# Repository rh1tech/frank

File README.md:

# FRANK

FRANK is a hardware emulation platform built around the Raspberry Pi RP2350 (Pico 2 modules and RP2350A QFN). RP2040 / Pico still works in FRANK's socket, but in practice only a handful of firmware (mainly the older ZX Spectrum cores) still targets RP2040. Everything modern (IBM PC, NES, SNES, Genesis, the DOOM / id Tech 1 ports, FRANK OS, and so on) is RP2350-only.

It started as a fork of the [Murmulator](https://murmulator.tilda.ws/) project by [Alex Ekb](https://t.me/Alex_Eburg). Over time it picked up extra video outputs, audio paths, USB and WiFi support, and several form factors.

The name comes from "Frankenstein". The board is stitched together from parts of different projects, so the name stuck.

## Looking for an older board?

This repository now ships only the boards under `hardware/` that are actively maintained. The `accessories/` and `archive/` directories are gone. Older revisions, retired boards, and accessory adapters such as HDMI2VGA and USB2PS2 live in [rh1tech/frank-archive](https://github.com/rh1tech/frank-archive).

Experimental and work-in-progress designs live in [rh1tech/frank-lab](https://github.com/rh1tech/frank-lab).

## The boards in this repo

Ten maintained boards and one published prototype, each with its own KiCad project, gerbers, BOM and assembly drawings, plus two add-on modules ([TurboSound](#modules) and [Hecate](#modules)) and three [retro-CPU boards](#retro-cpu-boards).

| Board | Render | PCB size | Compute | Best for |
|-------|:------:|----------|---------|----------|
| [FRANK Next](./hardware/frank_next) |  | 99.0 × 53.98 mm | RP2350B + RP2350A, both on-board | **Flagship.** Two RP2350 dies, on-board ESP8266EX WiFi, CH343P console, three USB-A host ports. |
| [MegaFRANK](./hardware/megafrank) |  | 149.9 × 99.5 mm | Pimoroni PGA2350 (RP2350B module) | Maximal board — every output plus on-board dual-AY TurboSound, DS3231 RTC and dual power input. |
| [FRANK PGA](./hardware/frank_pga) |  | 99.5 × 83.1 mm | Pimoroni PGA2350 (RP2350A module) | Every output on one PCB, native USB host with multiplexer, ESD-protected. |
| [FRANK](./hardware/frank) |  | 99.5 × 83.1 mm | Raspberry Pi Pico / Pico 2 (socket) + RP2040-Zero | Socketed alternative. Easiest to solder, swap Pico modules at will, USB-to-PS/2 helper on board. |
| [Old Skool FRANK](./hardware/oldskool) |  | 100.0 × 79.0 mm | Pimoroni PGA2350 (RP2350B module) | The retro-connector board: HDMI **and** VGA, hardware PS/2, DB9 gamepad. Only 2-layer design, easiest to hand-assemble. |
| [MiniFRANK](./hardware/minifrank) |  | 85.6 × 53.98 mm | RP2350A QFN, on-board | Compact full-feature board with WiFi, VGA, HDMI and one gamepad port. |
| [FRANK Core 2U](./hardware/frank_core2u) |  | 67.0 × 55.0 mm | RP2350B + RP2350A, both on-board | Smallest usable dual-die board. Video, sound, storage and USB only — no WiFi, no RTC. |
| [FRANK Core 2 Proto](./hardware/frank_core2_proto) |  | 55.0 × 55.0 mm | RP2350B + RP2350A, both on-board | Prototype. Core 2U without the USB host side — the dual-die topology at its smallest. |
| [MicroFRANK](./hardware/microfrank) |  | 32 × 74 mm | RP2350A QFN, on-board | Smallest single-die board. HDMI only, no hardware PS/2 or DB9 gamepad. Keyboards, mice and gamepads connect over the stacked USB host. |
| [ZeroFRANK](./hardware/zerofrank) |  | 65 × 25 mm | RP2350A QFN, on-board | Smallest RP2350A board. HDMI only, USB host for input, on-board flash + PSRAM + I²S audio. |
| [Nyx](./hardware/nyx) |  | 51 × 21 mm | RP2350B QFN, on-board | Open-source Pico 2 clone with built-in PSRAM. Drop-in replacement for Pico Plus 2 in the FRANK socket. |

The full-size and compact boards use the M2 GPIO layout, so any firmware build for M2 runs on them (subject to the feature differences below). FRANK Next, Core 2U and Core 2 Proto are the exception: they carry two RP2350 dies and firmware must be built for that split, or the slave simply sits idle. Nyx is a compute module — it plugs into the FRANK socket and provides the RP2350B, flash and PSRAM; the FRANK motherboard provides all the I/O.

### Comparison: full-size boards

| Feature | MegaFRANK | FRANK PGA | FRANK | Old Skool |
|---------|:---------:|:---------:|:-----:|:---------:|
| Compute | Pimoroni PGA2350 | Pimoroni PGA2350 | Pico / Pico 2 (socket) | Pimoroni PGA2350 |
| Copper layers | 4 | 4 | 4 | **2** |
| On-board flash | via module | via module | via module | via module |
| On-board PSRAM | via module | via module | via module | via module |
| HDMI output | Yes | Yes | Yes | Yes |
| VGA output | Yes | Yes | Yes | Yes |
| Composite (RCA) | Yes | Yes | Yes | — |
| TFT display header | Yes | Yes | Yes | — |
| Hardware PS/2 port | Yes | Yes | Yes | Yes |
| USB-emulated PS/2 (RP2040-Zero) | — | — | Yes | — |
| Gamepad ports (DB9) | 2 | 2 | 2 | 1 |
| Stacked USB Type-A host | Yes | Yes | Yes | Yes |
| USB hub | MW7211A | MW7211A | MW7211A | MW7211A |
| USB host multiplexer | 74HC4052D | 74HC4052D | — | 74HC4052 |
| USBLC6 ESD protection | Yes | Yes | — | — |
| WiFi | ESP-01S socket | ESP-01S socket | ESP-01S socket | ESP-01S socket |
| Real-time clock | DS3231 | — | — | — |
| Tape input (3.5mm) | Yes | Yes | Yes | Yes |
| Audio DAC | TDA1387 | TDA1387 | TDA1387 | TDA1545A + LM358 |
| PAM8403 speaker amp | Yes | Yes | Yes | — |
| Power input | DC barrel jack (×2) | DC barrel jack | DC barrel jack | USB-C / USB-B |
| Voltage regulator | MP1584 buck + AMS1117 LDO | MP1584 buck + AMS1117 LDO | MP1584 buck + AMS1117 LDO | AMS1117 LDO |
| Mounting holes | 4 × 2.7 mm | 4 × 2.7 mm | 4 × 2.7 mm | 4 × 2.7 mm |

On-board TurboSound (dual YM2149), a DS3231 real-time clock and a DS2401 silicon serial number are unique to MegaFRANK. Old Skool FRANK is the only 2-layer board in the repo, which makes it the friendliest to hand-assembly and rework.

### Comparison: compact boards

| Feature | FRANK Next | MiniFRANK | Core 2U | Core 2 Proto | MicroFRANK | ZeroFRANK |
|---------|:----------:|:---------:|:-------:|:------------:|:----------:|:---------:|
| Compute | RP2350B + RP2350A | RP2350A QFN | RP2350B + RP2350A | RP2350B + RP2350A | RP2350A QFN | RP2350A QFN |
| On-board flash | 2 × W25Q128 | W25Q128 | 2 × W25Q128 | 2 × W25Q128 | W25Q128 | W25Q128 |
| On-board PSRAM | 2 × 8 MB | 8 MB | 2 × 8 MB | 2 × 8 MB | 8 MB | 8 MB |
| HDMI output | Yes | Yes | Yes | Yes | Yes | Yes |
| VGA output | — | Yes | — | — | — | — |
| Hardware PS/2 port | — | Yes | — | — | — | — |
| Gamepad ports (DB9) | — | 1 | — | — | — | — |
| USB Type-A host ports | 3 | 2 (stacked) | 2 | — | 2 (stacked) | — (USB-C PIO host) |
| USB hub | CH334F | MW7211A | MW7211A | — | MW7211A | — |
| USB host multiplexer | TS3USB221 × 2 | TS3USB221 | TS3USB221 | — | TS3USB221 | — |
| USB serial bridge | CH343P | — | — | — | — | — |
| WiFi | ESP8266EX on-board | ESP-01S socket | — | — | — | — |
| Real-time clock | DS3231MZ | — | — | — | — | — |
| Tape input (3.5mm) | Yes | Yes | Yes | — | — | — |
| Audio DAC | TLV320DAC3100 | TDA1387 | TDA1387T + LM358 | TDA1387T + LM358 | TDA1387 | TDA1387 |
| Power input | USB-C | USB-C | USB-C | USB-C × 2 | USB-C | USB-C |
| Voltage regulator | SY8089 buck | AMS1117 LDO | AMS1117 LDO | AMS1117 LDO | ME6211 LDO | AMS1117 LDO |
| Mounting holes | 4 × 2.5 mm plated | 4 × 2.7 mm | 4 × 2.5 mm plated | 4 × 2.5 mm plated | 4 × 2.7 mm | 4 × 2.7 mm |

FRANK Next, Core 2U and Core 2 Proto share the dual-RP2350 architecture: an RP2350B master for emulation and an RP2350A slave for USB host, audio and housekeeping. Core 2U and Core 2 Proto come from a different subsystem generation than FRANK Next — ESP-PSRAM64H memory, a discrete TDA1387T audio chain instead of the TLV320DAC3100 codec, an AMS1117 LDO instead of a switching buck, and no WiFi or RTC. Core 2 Proto is Core 2U minus its host side: same two dies, no hub, no USB-A, no tape input and no power switch.

## Retro CPU boards

These are not emulation boards. Each carries a real vintage CPU in a DIP-40 socket, with an RP2350B acting as the chipset — memory, video, storage and I/O. They do not run the FRANK emulation firmware; each has its own chipset firmware.

| Board | Render | PCB size | CPU | Notes |
|-------|:------:|----------|-----|-------|
| [XT8086 Alpha](./hardware/xt8086_alpha) |  | 99.9 × 78.0 mm | Intel 8086 (minimum mode) | The earlier 8086 design: PGA2350 module, VGA and composite outputs. Superseded by XT8086 Beta, now in [frank-lab](https://github.com/rh1tech/frank-lab). |

### Modules

Two add-on modules ship alongside the boards:

| Module | Render | PCB size | What it is |
|--------|:------:|----------|------------|
| [TurboSound](./hardware/turbosound) |  | 42 × 79.5 mm | Dual YM2149 / AY-3-8910 sound expansion (socketed DIP-40). **Currently supported only by [MiniFRANK](./docs/minifrank.md)** via its expansion header. |
| [Hecate](./hardware/hecate) |  | 53 × 29 mm | Standalone RP2040 USB-to-PS/2 bridge board. Runs the [Hecate firmware](https://github.com/rh1tech/hecate); presents USB keyboards and mice as PS/2 devices. |

## Supported software

Over thirty emulators and native ports run on FRANK boards.

### Console emulators

| Firmware | Platform | Repository | PSRAM required |
|----------|----------|------------|----------------|
| frank-nes | NES / Famicom (Dendy) | [frank-nes](https://github.com/rh1tech/frank-nes) | Yes (8 MB) |
| frank-snes | SNES / Super Famicom | [frank-snes](https://github.com/rh1tech/frank-snes) | Yes (8 MB) |
| frank-genesis | Sega Genesis / Mega Drive | [frank-genesis](https://github.com/rh1tech/frank-genesis) | Yes (8 MB) |
| frank-c64 | Commodore 64 | [frank-c64](https://github.com/rh1tech/frank-c64) | Yes (8 MB) |
| frank-apple | Apple IIe | [frank-apple](https://github.com/rh1tech/frank-apple) | Optional |
| frank-msx | MSX / MSX2 / MSX2+ (fMSX core) | [frank-msx](https://github.com/rh1tech/frank-msx) | Yes (8 MB) |

### PC emulation

| Firmware | Platform | Repository | PSRAM required |
|----------|----------|------------|----------------|
| frank-386 | IBM PC i386 (DOS, Windows 3.x/95, Linux) | [frank-386](https://github.com/rh1tech/frank-386) | Yes (8 MB) |

### Game engine ports

| Firmware | Game | Repository | PSRAM required |
|----------|------|------------|----------------|
| frank-idtech1 | DOOM, Heretic, Hexen, Strife (all-in-one) | [frank-idtech1](https://github.com/rh1tech/frank-idtech1) | Yes (8 MB) |
| frank-doom | DOOM (standalone) | [frank-doom](https://github.com/rh1tech/frank-doom) | Yes (8 MB) |
| frank-heretic | Heretic | [frank-heretic](https://github.com/rh1tech/frank-heretic) | Yes (8 MB) |
| frank-wolf3d | Wolfenstein 3D | [frank-wolf3d](https://github.com/rh1tech/frank-wolf3d) | Yes (8 MB) |
| frank-duke3d | Duke Nukem 3D | [frank-duke3d](https://github.com/rh1tech/frank-duke3d) | Yes (8 MB) |
| frank-prince | Prince of Persia | [frank-prince](https://github.com/rh1tech/frank-prince) | Yes (8 MB) |
| frank-digger | Digger Remastered | [frank-digger](https://github.com/rh1tech/frank-digger) | No |
| frank-quest | ScummVM (AGI, SCI, SCUMM v1–v7, GOB, KYRA — King's Quest, Monkey Island, Day of the Tentacle, Full Throttle, Gobliiins, Kyrandia and more) | [frank-quest](https://github.com/rh1tech/frank-quest) | Yes (8 MB) |

### OS and utilities

| Firmware | Description | Repository | PSRAM required |
|----------|-------------|------------|----------------|
| frank-os | Full desktop OS (Windows 95-style GUI, apps, built-in emulators) | [frank-os](https://github.com/rh1tech/frank-os) | Yes (8 MB) |
| frank-kickstart | UF2 firmware launcher with SD card browser | [frank-kickstart](https://github.com/rh1tech/frank-kickstart) | Optional |
| frank-manul | Text-mode web browser (HTTP/HTTPS via ESP-01 WiFi) | [frank-manul](https://github.com/rh1tech/frank-manul) | Yes (8 MB) |
| frank-netcard | AT modem firmware for the ESP-01 WiFi module | [frank-netcard](https://github.com/rh1tech/frank-netcard) | No |

### Murmulator firmware

The original [Murmulator](https://murmulator.ru/) project provides additional firmware that runs on FRANK boards as well:

**ZX Spectrum cores:** ZX Spectrum 48K / 128K / +3e (tecnocat, pico-spec, frut-bat, ZX Speccy P, murmulator), ZX Elf (pico-alf).

**Other cross-platform emulators:** MS-DOS IBM PC XT 8088, BK-0010 / BK-0011M, Radio 86RK, Macintosh, Atari 800, NES / Famicom / Dendy, Sega Master System / Game Gear, NEC PC Engine / TurboGrafx-16, Nintendo GameBoy / GameBoy Color, Watara Supervision, Atari Lynx, Bandai Wonderswan / Wonderswan Color, NeoGeo Pocket Color, Gamate, Game & Watch / Elektronika.

**Tools and applications:** MurmulatorOS, Picomite MMBasic, VersaTerm, the original Murmulator bootloader.

### Other compatible boards

Most firmware also runs on:

- Murmulator (M1 and M2)
- Olimex PICO-PC (some firmware)
- Waveshare RP2350-PiZero (some firmware)

## Getting started

1. Order or fab the PCB (gerbers are in each board's `gerbers/` directory).
2. Source the components using the BOM (`hardware/<board>/docs/<rev>/bom.html`).
3. Solder following the [board-specific guide](./docs/), starting with the smallest passives and working outwards.
4. Flash firmware: hold BOOTSEL on the RP chip, plug USB, release, copy a `.uf2` file to the drive that appears (or use `picotool load`).
5. Insert an SD card with ROMs, WADs or disk images.
6. Plug in a display (HDMI or VGA), keyboard (PS/2 or USB) and gamepad.

For quick switching between firmware, flash [frank-kickstart](https://github.com/rh1tech/frank-kickstart) first. It gives you a graphical launcher that re-flashes from SD without touching BOOTSEL again.

## PSRAM

Most modern firmware (frank-os, frank-quest, frank-386, frank-genesis, frank-snes, frank-msx, frank-idtech1, frank-doom and so on) needs 8 MB of PSRAM. Some firmware refuses to boot without it: frank-quest installs a custom dlmalloc backed entirely by external PSRAM (`drivers/psram_init.c`, `drivers/dlmalloc.c`), because the runtime (heap-allocated game state, decoded resources, mixer ring buffers, font caches) does not fit in the RP2350's 520 KB of SRAM.

How you get PSRAM depends on the board:

- **FRANK Next, Core 2U and Core 2 Proto**: 8 MB PSRAM per die, both dies on-board. Nothing to do.
- **MiniFRANK, MicroFRANK and ZeroFRANK**: PSRAM is already on-board (8 MB). Nothing to do.
- **FRANK PGA, MegaFRANK and Old Skool FRANK**: the Pimoroni PGA2350 module already includes 8 MB PSRAM. Nothing to do.
- **FRANK**: the socketed Pico 2 has no PSRAM by default. Three ways to fix this:
  1. **Pimoroni Pico Plus 2 (recommended).** A ready-made Pico 2 with 8 MB PSRAM. Drop it into the socket and you are done.
  2. **Build a [Nyx](./hardware/nyx)**, an open-source RP2350B board with integrated 16 MB flash and 8 MB PSRAM. Same form factor as Pico 2, drops straight into the socket.
  3. **Solder a PSRAM chip on top of the flash chip of an RP2350 clone.** SOP-8 flash chips are mostly only on clones (typically the black boards), not on a genuine Pico 2.

## Repo layout

```
hardware/      Board KiCad projects (frank_next, megafrank, frank_pga, frank,
               oldskool, minifrank, frank_core2u, frank_core2_proto, microfrank,
               zerofrank, nyx), the retro-CPU board xt8086_alpha, plus the turbosound and hecate modules
docs/          Shared component datasheets and assembly notes
software/      Pre-built UF2s. Currently ships Hecate, the USB-to-PS/2 bridge
               firmware for FRANK's on-board RP2040-Zero. Once flashed, a USB
               keyboard or mouse appears on the hardware PS/2 lines.
               Source: https://github.com/rh1tech/hecate
```

## Documentation

Each board and module has its own assembly and usage guide:

- [FRANK Next assembly and usage guide](./docs/frank_next.md)
- [MegaFRANK assembly and usage guide](./docs/megafrank.md)
- [FRANK PGA assembly and usage guide](./docs/frank_pga.md)
- [FRANK assembly and usage guide](./docs/frank.md)
- [Old Skool FRANK assembly and usage guide](./docs/oldskool.md)
- [MiniFRANK assembly and usage guide](./docs/minifrank.md)
- [FRANK Core 2U assembly and usage guide](./docs/frank_core2u.md)
- [FRANK Core 2 Proto assembly and usage guide](./docs/frank_core2_proto.md)
- [MicroFRANK assembly and usage guide](./docs/microfrank.md)
- [ZeroFRANK assembly and usage guide](./docs/zerofrank.md)
- [Nyx assembly and usage guide](./docs/nyx.md)
- [TurboSound module guide](./docs/turbosound.md)
- [Hecate (USB-to-PS/2 bridge) guide](./docs/hecate.md)

The `hardware/<board>/docs/` directories also contain auto-generated BOMs (`bom.html`) and assembly drawings (`assembly.pdf`, `schematics.pdf`) for each PCB revision.

## Links

- [rh1.tech/projects/frank](https://rh1.tech/projects/frank) — project website
- [rh1tech/frank-archive](https://github.com/rh1tech/frank-archive) — older boards and accessories
- [rh1tech/frank-lab](https://github.com/rh1tech/frank-lab) — experimental designs

### Firmware repositories

Console emulators:

- [frank-nes](https://github.com/rh1tech/frank-nes) — NES / Famicom (Dendy)
- [frank-snes](https://github.com/rh1tech/frank-snes) — SNES / Super Famicom
- [frank-genesis](https://github.com/rh1tech/frank-genesis) — Sega Genesis / Mega Drive
- [frank-c64](https://github.com/rh1tech/frank-c64) — Commodore 64
- [frank-apple](https://github.com/rh1tech/frank-apple) — Apple IIe
- [frank-msx](https://github.com/rh1tech/frank-msx) — MSX / MSX2 / MSX2+

PC emulation:

- [frank-386](https://github.com/rh1tech/frank-386) — IBM PC i386 (DOS, Windows 3.x/95, Linux)

Game engine ports:

- [frank-idtech1](https://github.com/rh1tech/frank-idtech1) — DOOM, Heretic, Hexen, Strife (all-in-one)
- [frank-doom](https://github.com/rh1tech/frank-doom) — DOOM (standalone)
- [frank-heretic](https://github.com/rh1tech/frank-heretic) — Heretic
- [frank-wolf3d](https://github.com/rh1tech/frank-wolf3d) — Wolfenstein 3D
- [frank-duke3d](https://github.com/rh1tech/frank-duke3d) — Duke Nukem 3D
- [frank-prince](https://github.com/rh1tech/frank-prince) — Prince of Persia
- [frank-digger](https://github.com/rh1tech/frank-digger) — Digger Remastered
- [frank-quest](https://github.com/rh1tech/frank-quest) — ScummVM (AGI, SCI, SCUMM, GOB, KYRA)

OS and utilities:

- [frank-os](https://github.com/rh1tech/frank-os) — Full desktop OS with built-in emulators
- [frank-kickstart](https://github.com/rh1tech/frank-kickstart) — UF2 firmware launcher
- [frank-manul](https://github.com/rh1tech/frank-manul) — Text-mode web browser
- [frank-netcard](https://github.com/rh1tech/frank-netcard) — AT modem firmware for ESP-01
- [hecate](https://github.com/rh1tech/hecate) — USB-to-PS/2 bridge for the RP2040-Zero

## Author

Mikhail Matveev — software engineer and hardware developer based in Thessaloniki, Greece. Background in software architecture, QA and open-source development. Builds retro computing hardware and writes firmware for fun. More projects at [rh1.tech](https://rh1.tech).

## License

&copy; 2026 Mikhail Matveev, <xtreme@rh1.tech>

GPL v3. See [LICENSE](./LICENSE).

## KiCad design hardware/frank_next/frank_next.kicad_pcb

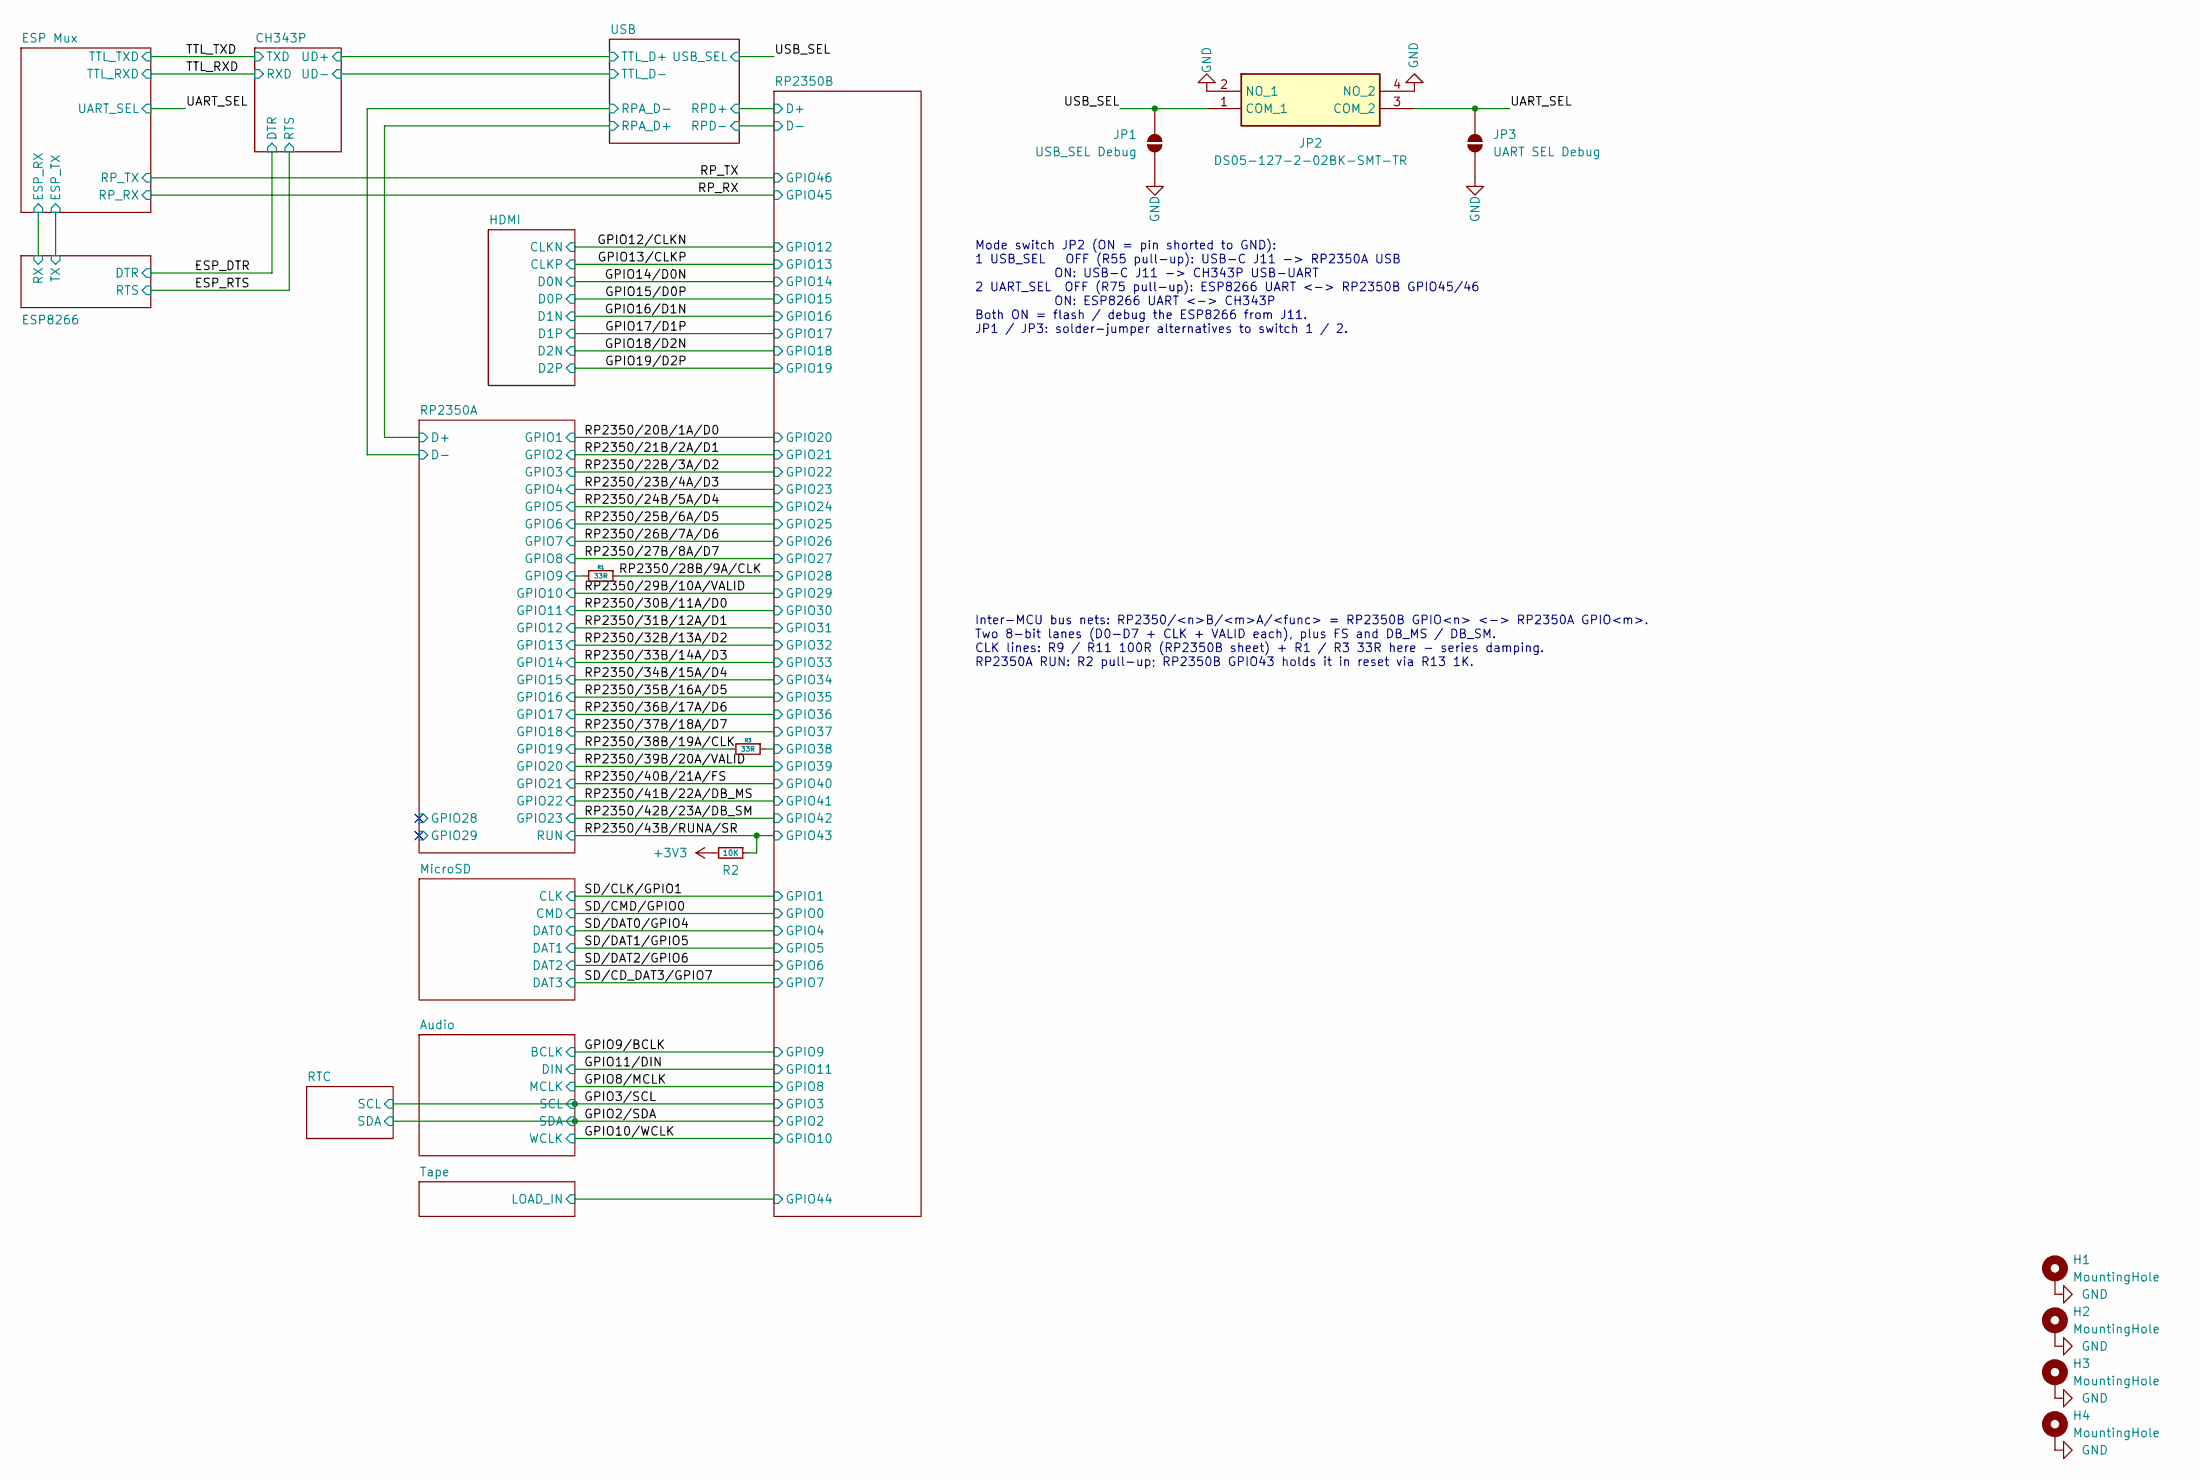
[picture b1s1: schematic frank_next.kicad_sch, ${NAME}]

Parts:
H1, H2, H3, H4: MountingHole; MountingHole_2.5mm_Pad_Via
JP1: USB_SEL Debug; SolderJumper-2_P1.3mm_Open_RoundedPad1.0x1.5mm
JP2: DS05-127-2-02BK-SMT-TR; SW_DS05-127-2-02BK-SMT-TR; Mouser Part Number 490-DS05127202BK-STR
JP3: UART SEL Debug; SolderJumper-2_P1.3mm_Open_RoundedPad1.0x1.5mm
R1, R3: 33R; R_0603_1608Metric; LCSC C23140
R2: 10K; R_0603_1608Metric; LCSC C2906982

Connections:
+3V3: R2.2; also elsewhere on the board
/RP2350A/GPIO9: R1.2; also elsewhere on the board
/RP2350B/GPIO38: R3.1; also elsewhere on the board
/RP2350/28B/9A/CLK: R1.1; also elsewhere on the board
/RP2350/38B/19A/CLK: R3.2; also elsewhere on the board
/RP2350/43B/RUNA/SR: R2.1; also elsewhere on the board
/UART_SEL: JP2.3 (COM_2), JP3.2 (B); also elsewhere on the board
/USB_SEL: JP1.2 (B), JP2.1 (COM_1); also elsewhere on the board
GND: H1.1 (1_1), H2.1 (1_1), H3.1 (1_1), H4.1 (1_1), JP1.1 (A), JP2.2 (NO_1), JP2.4 (NO_2), JP3.1 (A); also elsewhere on the board

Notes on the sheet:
Inter-MCU bus nets: RP2350/<n>B/<m>A/<func> = RP2350B GPIO<n> <-> RP2350A GPIO<m>. Two 8-bit lanes (D0-D7 + CLK + VALID each), plus FS and DB_MS / DB_SM. CLK lines: R9 / R11 100R (RP2350B sheet) + R1 / R3 33R here - series damping. RP2350A RUN: R2 pull-up; RP2350B GPIO43 holds it in reset via R13 1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
Mode switch JP2 (ON = pin shorted to GND): 1 USB_SEL OFF (R55 pull-up): USB-C J11 -> RP2350A USB ON: USB-C J11 -> CH343P USB-UART 2 UART_SEL OFF (R75 pull-up): ESP8266 UART <-> RP2350B GPIO45/46 ON: ESP8266 UART <-> CH343P Both ON = flash / debug the ESP8266 from J11. JP1 / JP3: solder-jumper alter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

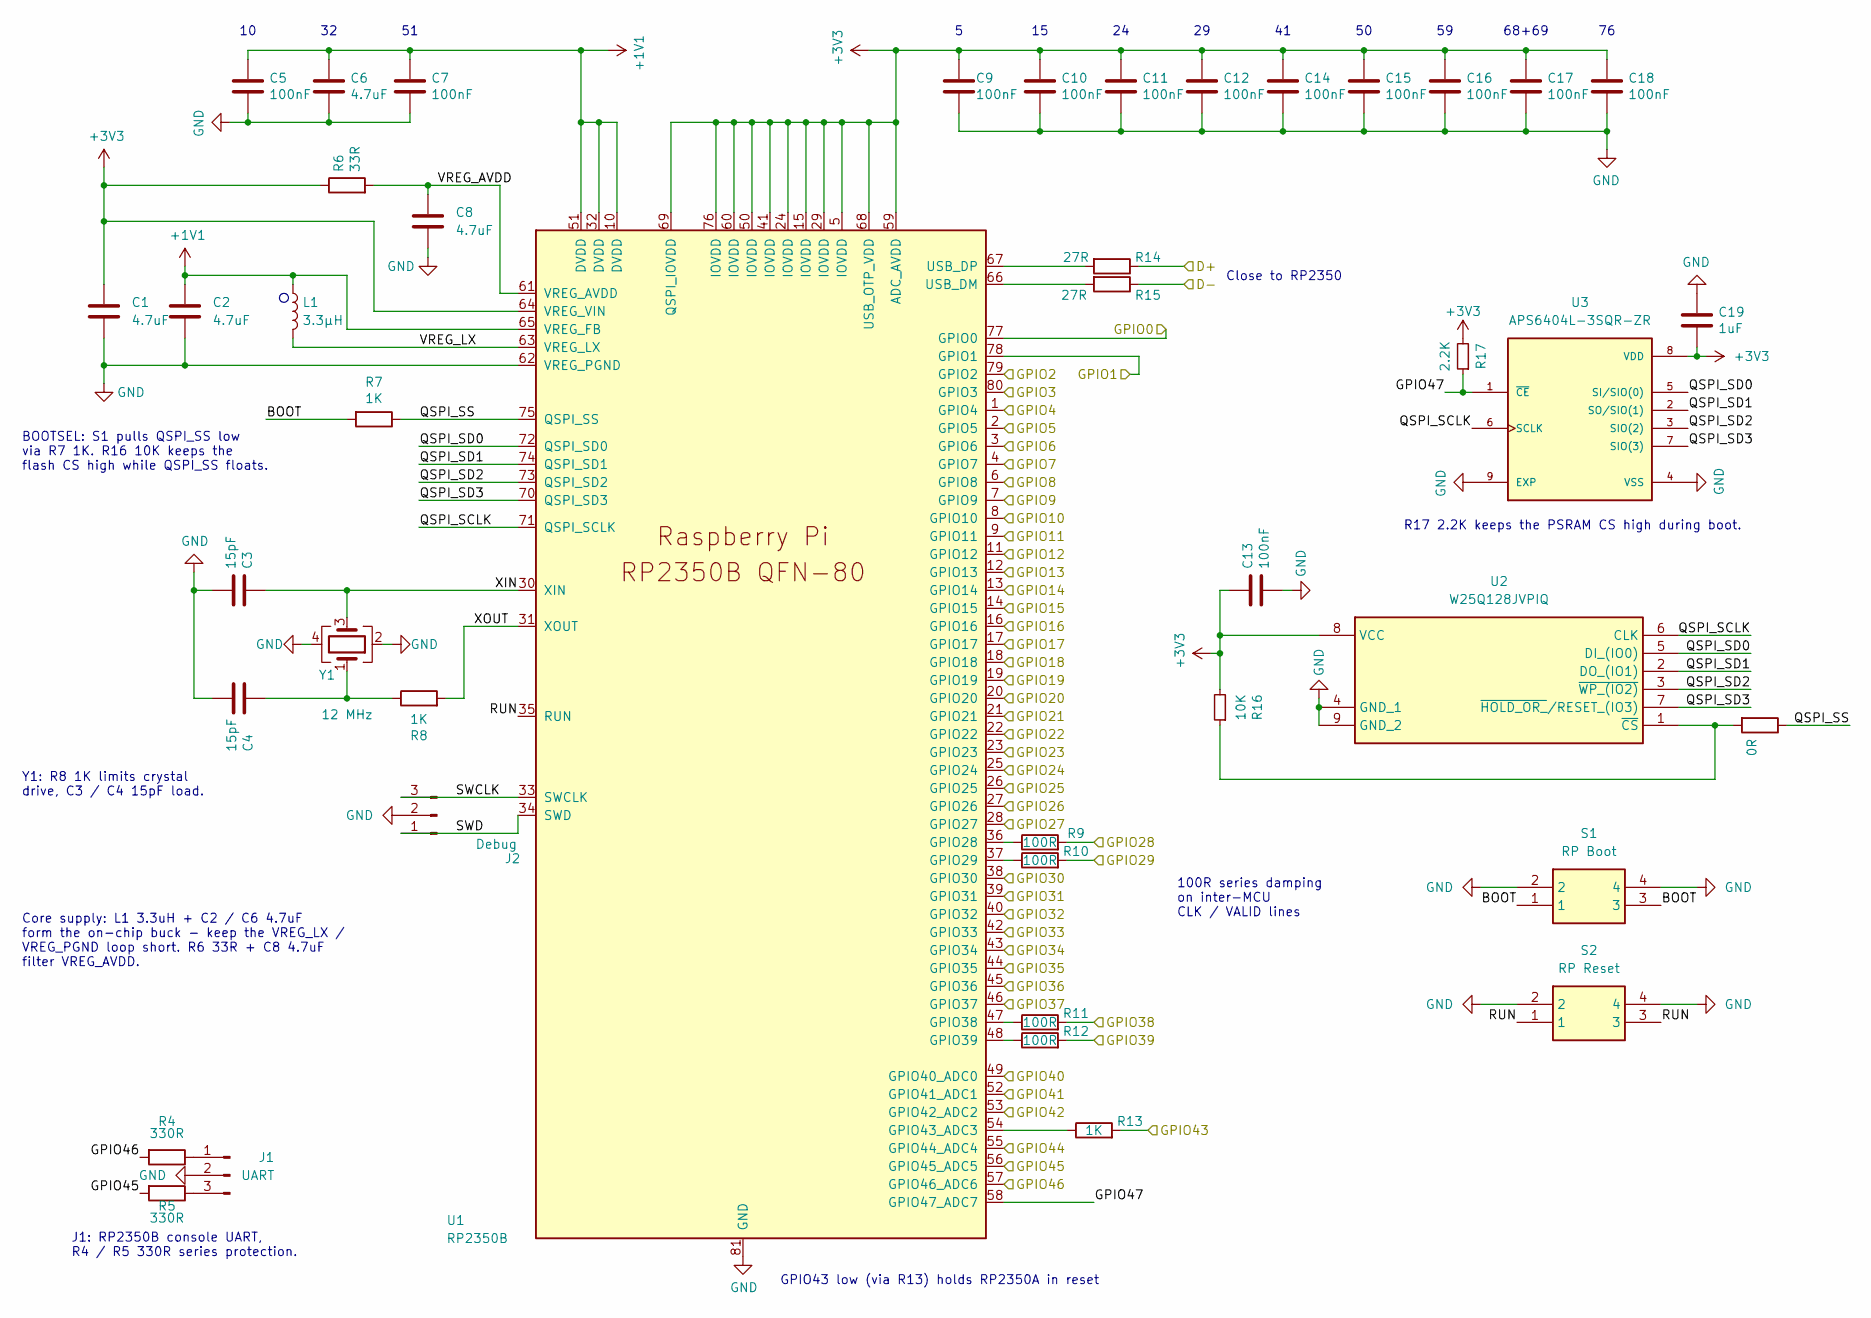
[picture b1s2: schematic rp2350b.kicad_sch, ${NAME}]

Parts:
C1, C2, C6, C8: 4.7uF; C_0603_1608Metric; LCSC C5360844
C3, C4: 15pF; C_0603_1608Metric; LCSC C1644
C5, C7, C9, C10, C11, C12, C13, C14, C15, C16, C17, C18: 100nF; C_0603_1608Metric; LCSC C14663
C19: 1uF; C_0603_1608Metric; LCSC C5199872
J1: UART; JST_SH_1x03_P1.00mm_Vertical; LCSC C160389
J2: Debug; JST_SH_1x03_P1.00mm_Vertical; LCSC C160389
L1: 3.3µH; L_AOTA-B201610_2.0x1.6mm; LCSC C42411119
R4, R5: 330R; R_0603_1608Metric; LCSC C23138
R6: 33R; R_0603_1608Metric; LCSC C23140
R7, R8, R13: 1K; R_0603_1608Metric; LCSC C21190
R9, R10, R11, R12: 100R; R_0603_1608Metric; LCSC C22775
R14, R15: 27R; R_0603_1608Metric; LCSC C25190
R16: 10K; R_0603_1608Metric; LCSC C2906982
R17: 2.2K; R_0603_1608Metric; LCSC C4190
R18: 0R; R_0603_1608Metric; LCSC C21189
S1: RP Boot; Button_SMD_3x4x2mm; Mouser Part Number 611-KMR221G-LFS; LCSC C55200587
S2: RP Reset; Button_SMD_3x4x2mm; Mouser Part Number 611-KMR221G-LFS; LCSC C55200587
U1: RP2350B; RP2350-QFN-80_10x10_P0.4mm; LCSC C42415655
U2: W25Q128JVPIQ; WSON-8-1EP_6x5mm_P1.27mm_EP3.45x4.35mm; Mouser Part Number 454-W25Q128JVPIQ; LCSC C190862
U3: APS6404L-3SQR-ZR; PSON50P200X300X50-9N; PARTREV 2.3; LCSC C3040877
Y1: 12 MHz; Crystal_SMD_3225-4Pin_3.2x2.5mm; LCSC C20625731

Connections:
+1V1: C2.1, C5.1, C6.1, C7.1, L1.1, U1.10 (DVDD), U1.32 (DVDD), U1.51 (DVDD), U1.65 (VREG_FB)
+3V3: C1.1, C9.1, C10.1, C11.1, C12.1, C13.1, C14.1, C15.1, C16.1, C17.1, C18.1, C19.2, R6.1, R16.2, R17.2, U1.5 (IOVDD), U1.15 (IOVDD), U1.24 (IOVDD), U1.29 (IOVDD), U1.41 (IOVDD), U1.50 (IOVDD), U1.59 (ADC_AVDD), U1.60 (IOVDD), U1.64 (VREG_VIN), U1.68 (USB_OTP_VDD), U1.69 (QSPI_IOVDD), U1.76 (IOVDD), U2.8 (VCC), U3.8 (VDD); also elsewhere on the board
/GPIO2/SDA: U1.79 (GPIO2); also elsewhere on the board
/GPIO3/SCL: U1.80 (GPIO3); also elsewhere on the board
/GPIO8/MCLK: U1.6 (GPIO8); also elsewhere on the board
/GPIO9/BCLK: U1.7 (GPIO9); also elsewhere on the board
/GPIO10/WCLK: U1.8 (GPIO10); also elsewhere on the board
/GPIO11/DIN: U1.9 (GPIO11); also elsewhere on the board
/GPIO12/CLKN: U1.11 (GPIO12); also elsewhere on the board
/GPIO13/CLKP: U1.12 (GPIO13); also elsewhere on the board
/GPIO14/D0N: U1.13 (GPIO14); also elsewhere on the board
/GPIO15/D0P: U1.14 (GPIO15); also elsewhere on the board
/GPIO16/D1N: U1.16 (GPIO16); also elsewhere on the board
/GPIO17/D1P: U1.17 (GPIO17); also elsewhere on the board
/GPIO18/D2N: U1.18 (GPIO18); also elsewhere on the board
/GPIO19/D2P: U1.19 (GPIO19); also elsewhere on the board
/RP2350B/BOOT: R7.2, S1.1, S1.3
/RP2350B/D+: R14.1; also elsewhere on the board
/RP2350B/D-: R15.1; also elsewhere on the board
/RP2350B/GPIO38: R11.2; also elsewhere on the board
/RP2350B/GPIO44: U1.55 (GPIO44_ADC4); also elsewhere on the board
/RP2350B/GPIO47: R17.1, U1.58 (GPIO47_ADC7), U3.1 (~CE)
/RP2350B/QSPI_SCLK: U1.71 (QSPI_SCLK), U2.6 (CLK), U3.6 (SCLK)
/RP2350B/QSPI_SD0: U1.72 (QSPI_SD0), U2.5 (DI_(IO0)), U3.5 (SI/SIO(0))
/RP2350B/QSPI_SD1: U1.74 (QSPI_SD1), U2.2 (DO_(IO1)), U3.2 (SO/SIO(1))
/RP2350B/QSPI_SD2: U1.73 (QSPI_SD2), U2.3 (~WP_(IO2)), U3.3 (SIO(2))
/RP2350B/QSPI_SD3: U1.70 (QSPI_SD3), U2.7 (~HOLD_OR_/RESET_(IO3)), U3.7 (SIO(3))
/RP2350B/QSPI_SS: R7.1, R18.1, U1.75 (QSPI_SS)
/RP2350B/RUN: S2.1, S2.3, U1.35 (RUN)
/RP2350B/SWCLK: J2.3, U1.33 (SWCLK)
/RP2350B/SWD: J2.1, U1.34 (SWD)
/RP2350B/VREG_AVDD: C8.1, R6.2, U1.61 (VREG_AVDD)
/RP2350B/VREG_LX: L1.2, U1.63 (VREG_LX)
/RP2350B/XIN: C3.1, U1.30 (XIN), Y1.3
/RP2350B/XOUT: R8.2, U1.31 (XOUT)
/RP2350/20B/1A/D0: U1.20 (GPIO20); also elsewhere on the board
/RP2350/21B/2A/D1: U1.21 (GPIO21); also elsewhere on the board
/RP2350/22B/3A/D2: U1.22 (GPIO22); also elsewhere on the board
/RP2350/23B/4A/D3: U1.23 (GPIO23); also elsewhere on the board
/RP2350/24B/5A/D4: U1.25 (GPIO24); also elsewhere on the board
/RP2350/25B/6A/D5: U1.26 (GPIO25); also elsewhere on the board
/RP2350/26B/7A/D6: U1.27 (GPIO26); also elsewhere on the board
/RP2350/27B/8A/D7: U1.28 (GPIO27); also elsewhere on the board
/RP2350/28B/9A/CLK: R9.2; also elsewhere on the board
/RP2350/29B/10A/VALID: R10.2; also elsewhere on the board
/RP2350/30B/11A/D0: U1.38 (GPIO30); also elsewhere on the board
/RP2350/31B/12A/D1: U1.39 (GPIO31); also elsewhere on the board
/RP2350/32B/13A/D2: U1.40 (GPIO32); also elsewhere on the board
/RP2350/33B/14A/D3: U1.42 (GPIO33); also elsewhere on the board
/RP2350/34B/15A/D4: U1.43 (GPIO34); also elsewhere on the board
/RP2350/35B/16A/D5: U1.44 (GPIO35); also elsewhere on the board
/RP2350/36B/17A/D6: U1.45 (GPIO36); also elsewhere on the board
/RP2350/37B/18A/D7: U1.46 (GPIO37); also elsewhere on the board
/RP2350/39B/20A/VALID: R12.2; also elsewhere on the board
/RP2350/40B/21A/FS: U1.49 (GPIO40_ADC0); also elsewhere on the board
/RP2350/41B/22A/DB_MS: U1.52 (GPIO41_ADC1); also elsewhere on the board
/RP2350/42B/23A/DB_SM: U1.53 (GPIO42_ADC2); also elsewhere on the board
/RP2350/43B/RUNA/SR: R13.2; also elsewhere on the board
/RP_RX: R5.2, U1.56 (GPIO45_ADC5); also elsewhere on the board
/RP_TX: R4.2, U1.57 (GPIO46_ADC6); also elsewhere on the board
/SD/CD_DAT3/GPIO7: U1.4 (GPIO7); also elsewhere on the board
/SD/CLK/GPIO1: U1.78 (GPIO1); also elsewhere on the board
/SD/CMD/GPIO0: U1.77 (GPIO0); also elsewhere on the board
/SD/DAT0/GPIO4: U1.1 (GPIO4); also elsewhere on the board
/SD/DAT1/GPIO5: U1.2 (GPIO5); also elsewhere on the board
/SD/DAT2/GPIO6: U1.3 (GPIO6); also elsewhere on the board
GND: C1.2, C2.2, C3.2, C4.2, C5.2, C6.2, C7.2, C8.2, C9.2, C10.2, C11.2, C12.2, C13.2, C14.2, C15.2, C16.2, C17.2, C18.2, C19.1, J1.2, J2.2, S1.2, S1.4, S2.2, S2.4, U1.62 (VREG_PGND), U1.81 (GND), U2.4 (GND_1), U2.9 (GND_2), U3.4 (VSS), U3.9 (EXP), Y1.2, Y1.4; also elsewhere on the board
unnamed: C4.1, R8.1, Y1.1
unnamed: J1.1, R4.1
unnamed: J1.3, R5.1
unnamed: R9.1, U1.36 (GPIO28)
unnamed: R10.1, U1.37 (GPIO29)
unnamed: R11.1, U1.47 (GPIO38)
unnamed: R12.1, U1.48 (GPIO39)
unnamed: R13.1, U1.54 (GPIO43_ADC3)
unnamed: R15.2, U1.66 (USB_DM)
unnamed: R14.2, U1.67 (USB_DP)
unnamed: R16.1, R18.2, U2.1 (~CS)

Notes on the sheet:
J1: RP2350B console UART, R4 / R5 330R series protection.
BOOTSEL: S1 pulls QSPI_SS low via R7 1K. R16 10K keeps the flash CS high while QSPI_SS floats.
GPIO43 low (via R13) holds RP2350A in reset
100R series damping on inter-MCU CLK / VALID lines
Core supply: L1 3.3uH + C2 / C6 4.7uF form the on-chip buck - keep the VREG_LX / VREG_PGND loop short. R6 33R + C8 4.7uF filter VREG_AVDD.
Close to RP2350
R17 2.2K keeps the PSRAM CS high during boot.
68+69
Y1: R8 1K limits crystal drive, C3 / C4 15pF load.

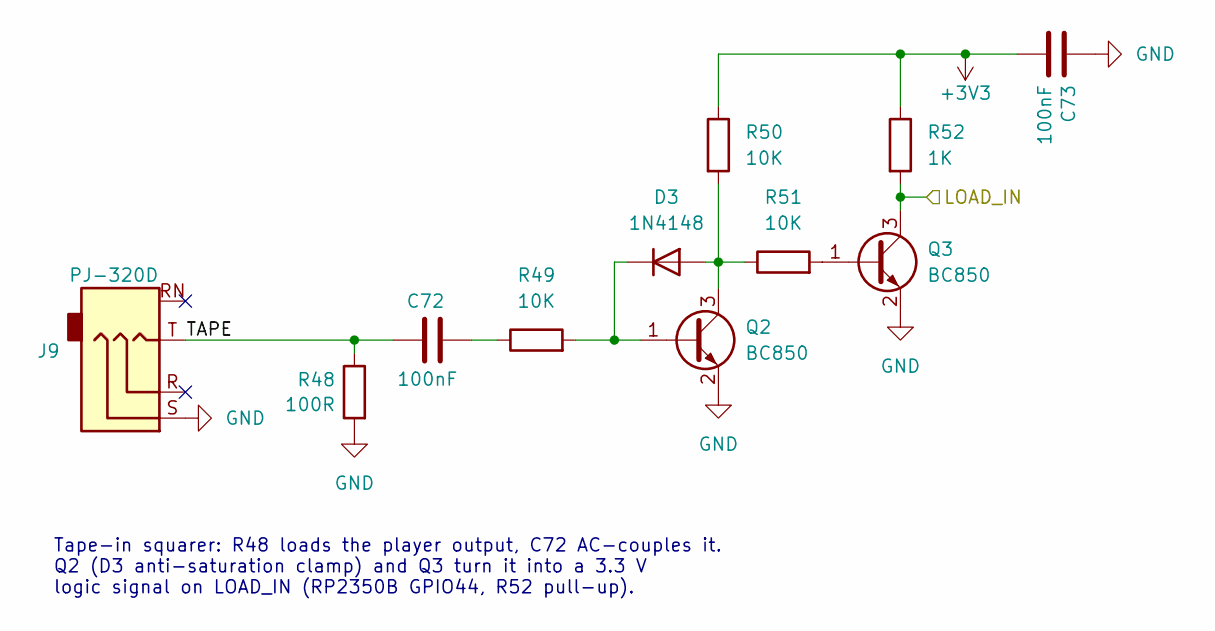
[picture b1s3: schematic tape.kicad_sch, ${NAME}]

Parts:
C72, C73: 100nF; C_0603_1608Metric; LCSC C14663
D3: 1N4148; D_SOD-323; LCSC C2128
J9: PJ-320D; AudioJack_3.5mm_PJ320D_TapeIn; LCSC C431535
Q2, Q3: BC850; SOT-23; LCSC C503377
R48: 100R; R_0603_1608Metric; LCSC C22775
R49, R50, R51: 10K; R_0603_1608Metric; LCSC C2906982
R52: 1K; R_0603_1608Metric; LCSC C21190

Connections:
+3V3: C73.2, R50.1, R52.1; also elsewhere on the board
/RP2350B/GPIO44: Q3.3 (C), R52.2; also elsewhere on the board
/Tape/TAPE: C72.1, J9.T, R48.1
GND: C73.1, J9.S, Q2.2 (E), Q3.2 (E), R48.2; also elsewhere on the board
unnamed: C72.2, R49.1
unnamed: D3.2 (A), Q2.3 (C), R50.2, R51.1
unnamed: D3.1 (K), Q2.1 (B), R49.2
unnamed: Q3.1 (B), R51.2

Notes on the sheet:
Tape-in squarer: R48 loads the player output, C72 AC-couples it. Q2 (D3 anti-saturation clamp) and Q3 turn it into a 3.3 V logic signal on LOAD_IN (RP2350B GPIO44, R52 pull-up).

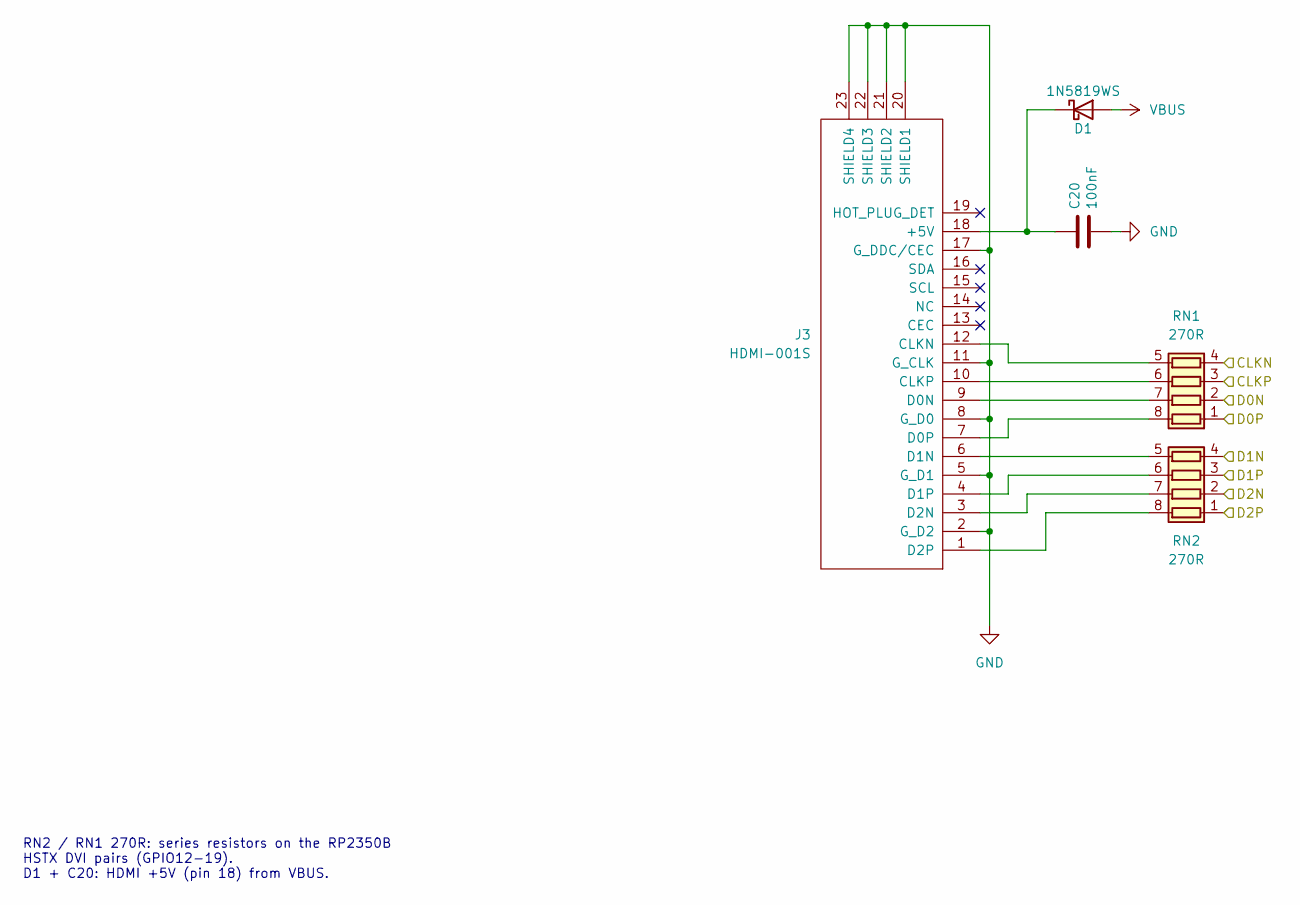
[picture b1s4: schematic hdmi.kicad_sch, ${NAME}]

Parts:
C20: 100nF; C_0603_1608Metric; LCSC C14663
D1: 1N5819WS; D_SOD-323; LCSC C191023
J3: HDMI-001S; HDMI_Female; LCSC C720616
RN1, RN2: 270R; R_Array_4x0603; LCSC C1731063

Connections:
/GPIO12/CLKN: RN1.4 (R4.1); also elsewhere on the board
/GPIO13/CLKP: RN1.3 (R3.1); also elsewhere on the board
/GPIO14/D0N: RN1.2 (R2.1); also elsewhere on the board
/GPIO15/D0P: RN1.1 (R1.1); also elsewhere on the board
/GPIO16/D1N: RN2.4 (R4.1); also elsewhere on the board
/GPIO17/D1P: RN2.3 (R3.1); also elsewhere on the board
/GPIO18/D2N: RN2.2 (R2.1); also elsewhere on the board
/GPIO19/D2P: RN2.1 (R1.1); also elsewhere on the board
GND: C20.2, J3.2 (G_D2), J3.5 (G_D1), J3.8 (G_D0), J3.11 (G_CLK), J3.17 (G_DDC/CEC), J3.20 (SHIELD1), J3.21 (SHIELD2), J3.22 (SHIELD3), J3.23 (SHIELD4); also elsewhere on the board
unnamed: C20.1, D1.1 (K), J3.18 (+5V)
unnamed: J3.12 (CLKN), RN1.5 (R4.2)
unnamed: J3.10 (CLKP), RN1.6 (R3.2)
unnamed: J3.9 (D0N), RN1.7 (R2.2)
unnamed: J3.7 (D0P), RN1.8 (R1.2)
unnamed: J3.6 (D1N), RN2.5 (R4.2)
unnamed: J3.4 (D1P), RN2.6 (R3.2)
unnamed: J3.3 (D2N), RN2.7 (R2.2)
unnamed: J3.1 (D2P), RN2.8 (R1.2)
VBUS: D1.2 (A); also elsewhere on the board

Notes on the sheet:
RN2 / RN1 270R: series resistors on the RP2350B HSTX DVI pairs (GPIO12-19). D1 + C20: HDMI +5V (pin 18) from VBUS.

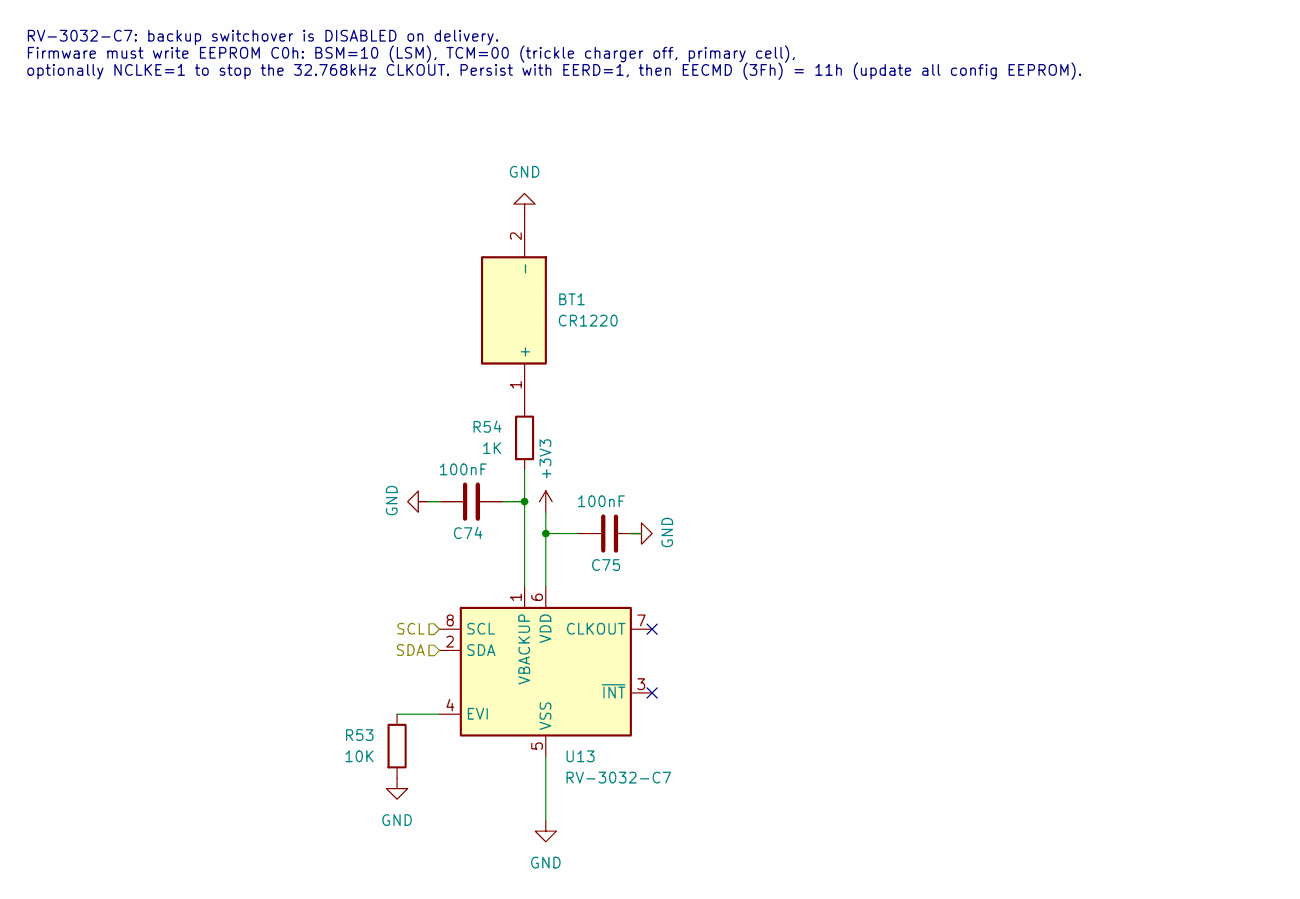
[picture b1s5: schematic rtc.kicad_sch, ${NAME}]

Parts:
BT1: CR1220; Battery_CR1220_MYOUNG_BS-12-B3AA003; Manufacturer_Part_Number BS-12-B3AA003; LCSC C964723
C74, C75: 100nF; C_0603_1608Metric; LCSC C14663
R53: 10K; R_0603_1608Metric; LCSC C2906982
R54: 1K; R_0603_1608Metric; LCSC C21190
U13: RV-3032-C7; LCSC C5127802

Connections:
+3V3: C75.1, U13.6 (VDD); also elsewhere on the board
/GPIO2/SDA: U13.2 (SDA); also elsewhere on the board
/GPIO3/SCL: U13.8 (SCL); also elsewhere on the board
GND: BT1.2 (-), C74.1, C75.2, R53.2, U13.5 (VSS); also elsewhere on the board
unnamed: BT1.1 (+), R54.1
unnamed: R53.1, U13.4 (EVI)
unnamed: C74.2, R54.2, U13.1 (VBACKUP)

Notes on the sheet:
RV-3032-C7: backup switchover is DISABLED on delivery. Firmware must write EEPROM C0h: BSM=10 (LSM), TCM=00 (trickle charger off, primary cell), optionally NCLKE=1 to stop the 32.768kHz CLKOUT. Persist with EERD=1, then EECMD (3Fh) = 11h (update all config EEPROM).

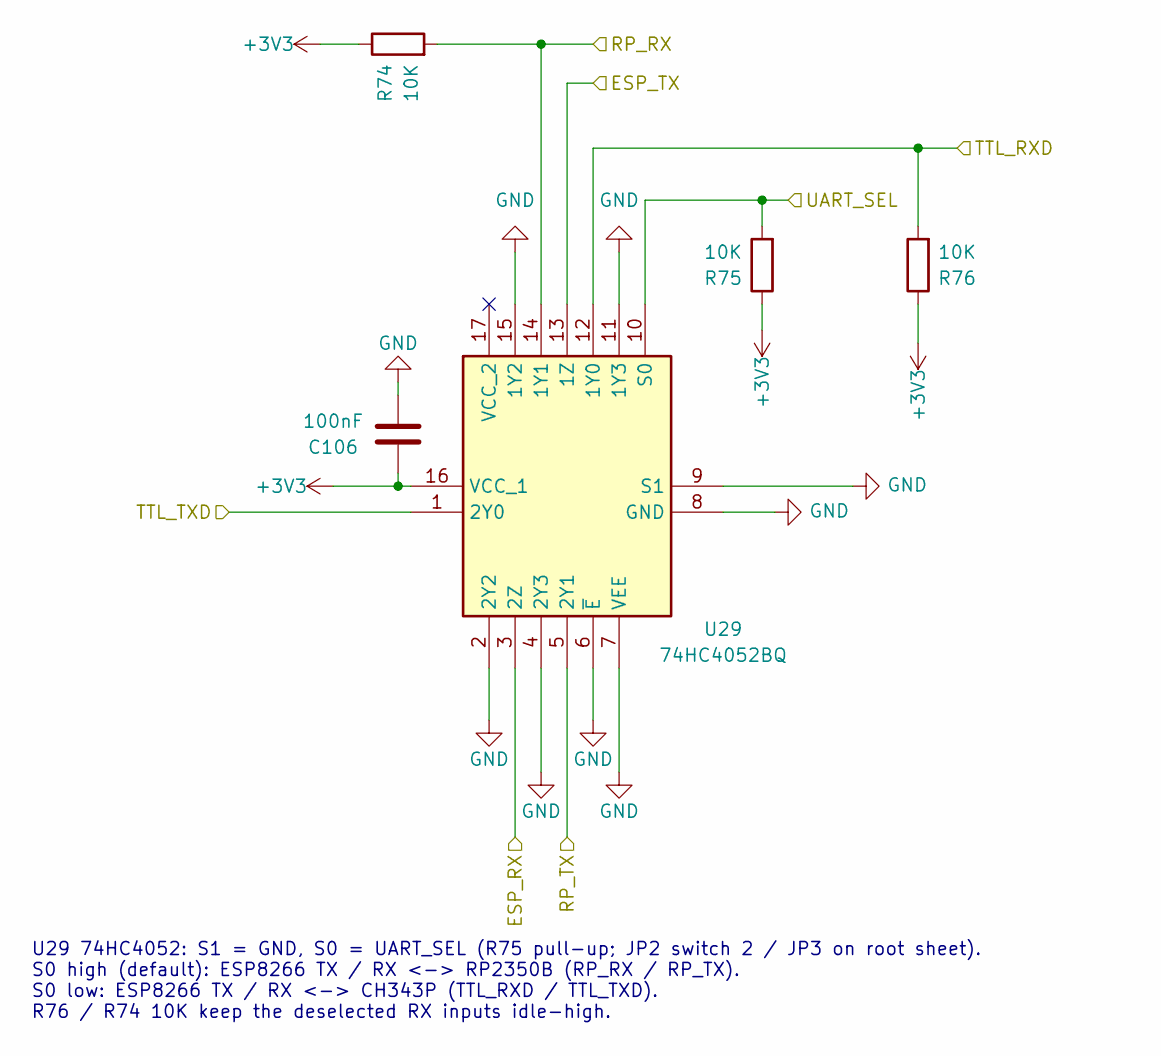
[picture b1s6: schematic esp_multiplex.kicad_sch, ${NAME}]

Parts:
C106: 100nF; C_0603_1608Metric; LCSC C14663
R74, R75, R76: 10K; R_0603_1608Metric; LCSC C2906982
U29: 74HC4052BQ; 74HC4052BQ115; Mouser Part Number 771-HC4052BQ115

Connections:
+3V3: C106.1, R74.1, R75.1, R76.1, U29.16 (VCC_1); also elsewhere on the board
/ESP8266/RX: U29.3 (2Z); also elsewhere on the board
/ESP8266/TX: U29.13 (1Z); also elsewhere on the board
/RP_RX: R74.2, U29.14 (1Y1); also elsewhere on the board
/RP_TX: U29.5 (2Y1); also elsewhere on the board
/TTL_RXD: R76.2, U29.12 (1Y0); also elsewhere on the board
/TTL_TXD: U29.1 (2Y0); also elsewhere on the board
/UART_SEL: R75.2, U29.10 (S0); also elsewhere on the board
GND: C106.2, U29.2 (2Y2), U29.4 (2Y3), U29.6 (~E), U29.7 (VEE), U29.8 (GND), U29.9 (S1), U29.11 (1Y3), U29.15 (1Y2); also elsewhere on the board

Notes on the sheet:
U29 74HC4052: S1 = GND, S0 = UART_SEL (R75 pull-up; JP2 switch 2 / JP3 on root sheet). S0 high (default): ESP8266 TX / RX <-> RP2350B (RP_RX / RP_TX). S0 low: ESP8266 TX / RX <-> CH343P (TTL_RXD / TTL_TXD). R76 / R74 10K keep the deselected RX inputs idle-high.
